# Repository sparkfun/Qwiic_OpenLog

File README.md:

SparkFun Qwiic OpenLog
========================================

[*SparkFun Qwiic OpenLog (DEV-15164)*](https://www.sparkfun.com/products/15164)

The [Qwiic](https://www.sparkfun.com/qwiic) system makes it easy to read all sorts of sensors, but what if you want to log that data? Qwiic OpenLog is an easy to use I2C based data logger. Simply write code like:

    recordToOpenLog("The battery voltage is:");
    recordToOpenLog(batteryVoltage);

And your data will be recorded to LOG00001.TXT for later review. 

The SparkFun Qwiic OpenLog is the smarter and better looking cousin to the extremely popular [OpenLog](https://www.sparkfun.com/products/13712). We've ported the serial based interface to I2C. Now you can daisy chain lots of I2C devices and log them all without taking up your serial port.

We've written a large number of example sketches to show how to record logs, create new logs, create and navigate directories, remove files and directories, and read the contents of files. 

Qwiic OpenLog supports clock stretching which means it performs even better than the original! Qwiic OpenLog will record data up to 21,000 bytes per second at 400kHz. As the receive buffer fills up QOL will hold the clock line letting the master know that it is busy. Once QOL is finished with a task it releases the clock allowing the data to continue flowing without corruption.

Need to get freaky and have multiple data loggers on the same bus? You're in luck. Qwiic OpenLog has both a solder jumper to allow for two devices on the same bus as well as a software setting to allow for the setting of any I2C address. Don't get too freaky though; the limit is 111 devices (0x08 to 0x77) on the same bus. Any microSD card will work so with 64GB cards you'll be limited to approximately 7 Terabytes of storage :(

We will be adding more features to the firmware over time and we've made it very easy to upgrade! If you're comfortable sending a sketch to an Uno then you can upgrade the firmware on Qwiic OpenLog.

Repository Contents
-------------------

* **/Firmware/Qwiic_OpenLog** - The core sketch that runs Qwiic OpenLog
* **/Hardware** - Eagle design files (.brd, .sch)

Documentation
--------------
* **[Library](https://github.com/sparkfun/SparkFun_Qwiic_OpenLog_Arduino_Library)** - Arduino library for the Qwiic OpenLog.
* **[Hookup Guide](https://learn.sparkfun.com/tutorials/qwiic-openlog-hookup-guide)** - Basic hookup guide for the Qwiic OpenLog.
* **[SparkFun Fritzing repo](https://github.com/sparkfun/Fritzing_Parts)** - Fritzing diagrams for SparkFun products.

License Information
-------------------

This product is _**open source**_! 

Please review the LICENSE.md file for license information. 

If you have any questions or concerns on licensing, please contact techsupport@sparkfun.com.

Please use, reuse, and modify these files as you see fit. Please maintain attribution to SparkFun Electronics and release any derivative under the same license.

Distributed as-is; no warranty is given.

- Your friends at SparkFun.

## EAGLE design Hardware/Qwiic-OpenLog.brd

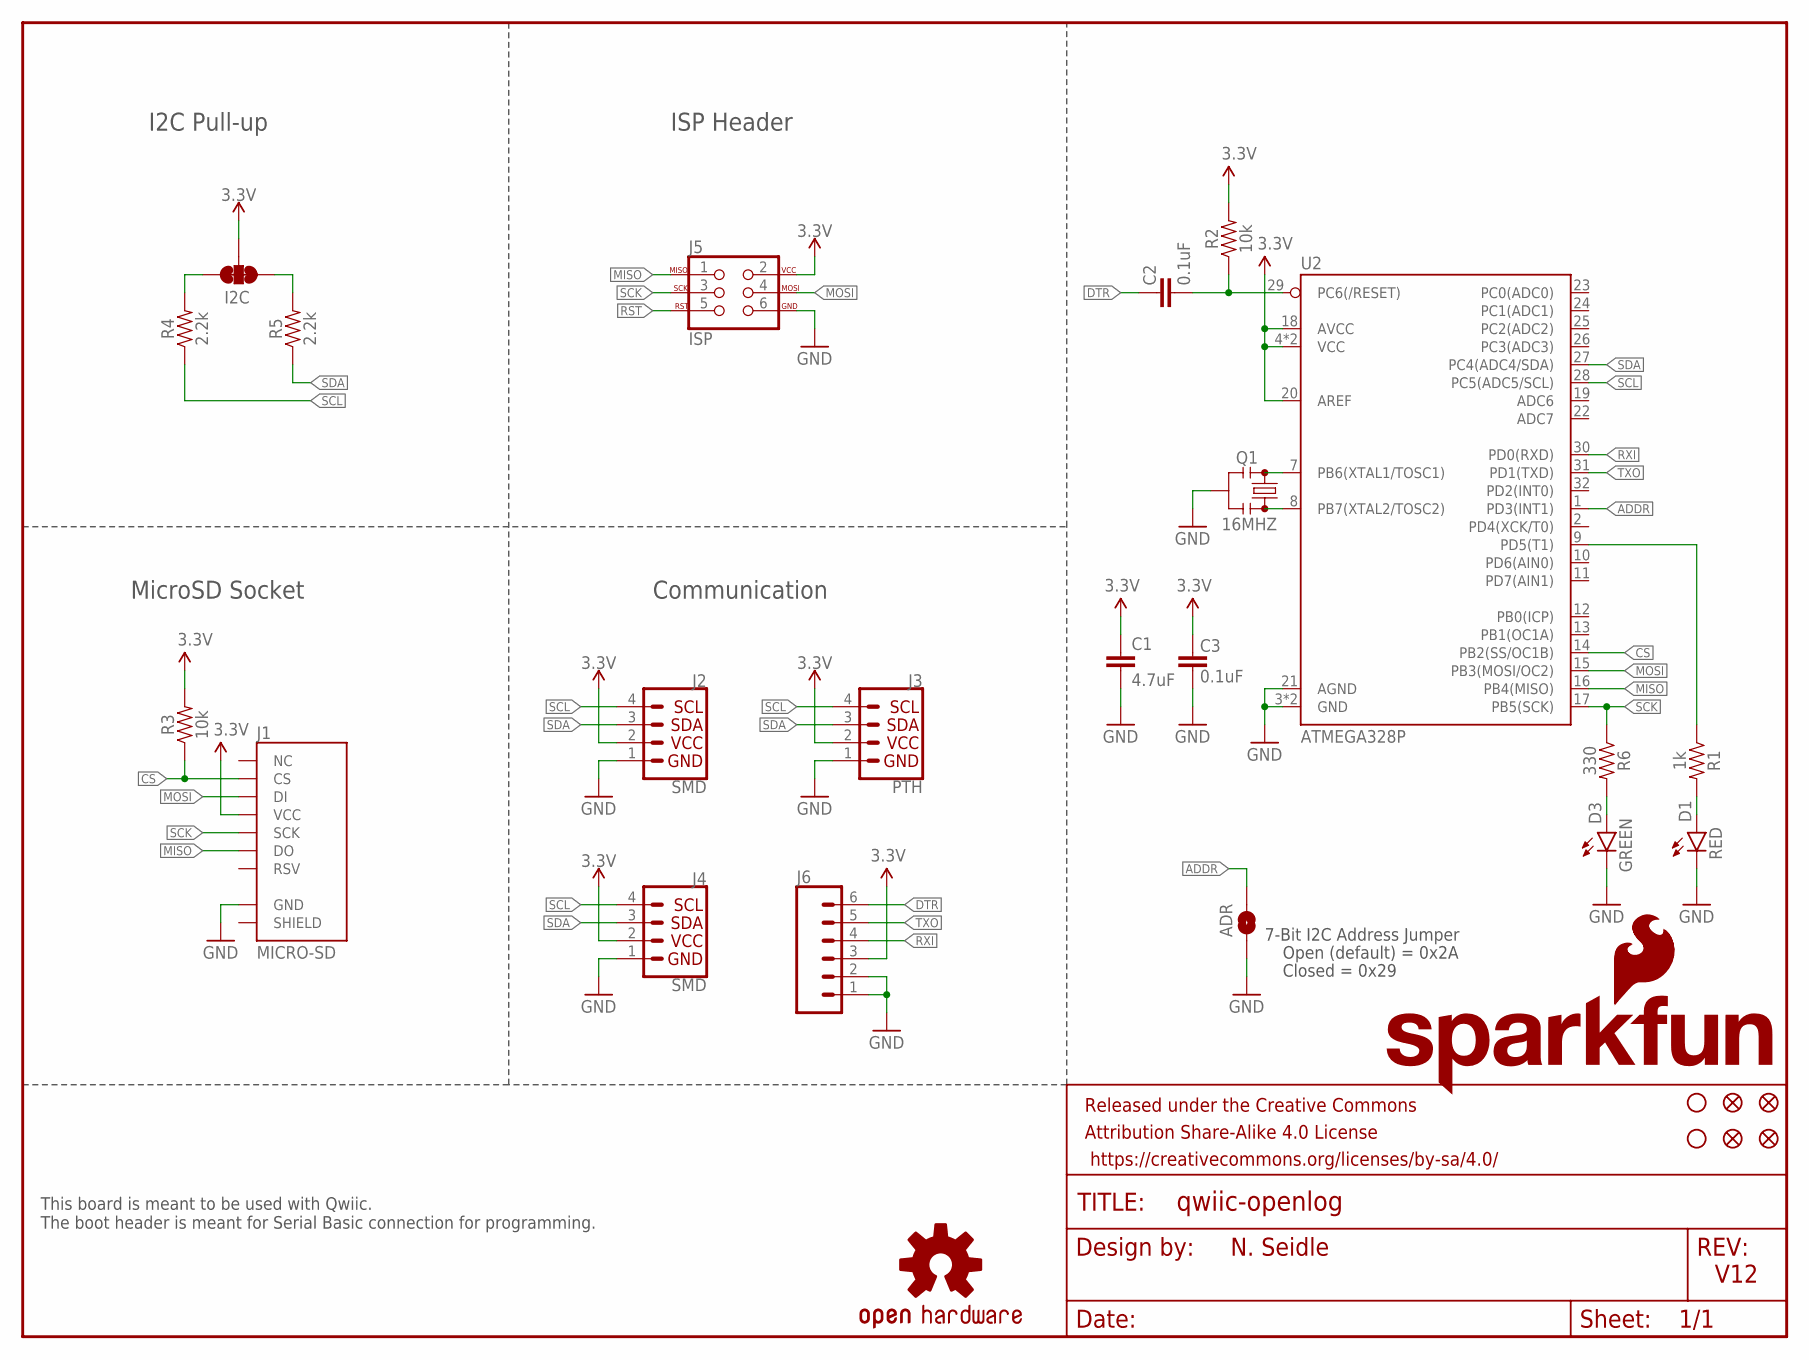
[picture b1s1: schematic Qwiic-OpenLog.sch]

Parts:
ADR: SOLDERJUMPERNO; SJ_2S-NO
C1: 4.7uF; 0603
C2, C3: 0.1uF; 0603
D1: RED; LED-0603
D3: GREEN; LED-0603
FID1, FID2, FID3, FID4: FIDUCIALUFIDUCIAL; FIDUCIAL-MICRO
FRAME1: FRAME-LETTER; CREATIVE_COMMONS
I2C: JUMPER-SMT_3_2-NC_TRACE_SILK; SMT-JUMPER_3_2-NC_TRACE_SILK
J1: MICRO-SD; MICRO-SD-SOCKET
J2, J4: SMD; 1X04_1MM_RA
J3: PTH; 1X04_NO_SILK
J5: ISP; 2X3_TEST_POINTS
J6: CONN_06NO_SILK_NO_POP; 1X06_NO_SILK
JP3, JP4: STAND-OFF
LOGO1: SFE_LOGO_FLAME.1_INCH; SFE_LOGO_FLAME_.1
LOGO2: OSHW-LOGOMINI; OSHW-LOGO-MINI
LOGO4: SFE_LOGO_NAME_FLAME.1_INCH; SFE_LOGO_NAME_FLAME_.1
Q1: 16MHZ; RESONATOR-SMD
R1: 1k; 0603
R2, R3: 10k; 0603
R4, R5: 2.2k; 0603
R6: 330; 0603
U2: ATMEGA328P; TQFP32-08

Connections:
3.3V: C1.1, C3.2, I2C.2, J1.VCC, J2.2, J3.2 (VCC), J4.2, J5.2, J6.3, R2.2, R3.2, U2.4 (VCC), U2.6 (VCC), U2.18 (AVCC), U2.20 (AREF)
ADDR: ADR.2, U2.1 (PD3(INT1))
CS: J1.CS, R3.1, U2.14 (PB2(SS/OC1B))
DTR: C2.2, J6.6
GND: ADR.1, C1.2, C3.1, D1.C, D3.C, J1.GND, J2.1, J3.1 (GND), J4.1, J5.6, J6.1, J6.2, Q1.2, U2.3 (GND), U2.5 (GND), U2.21 (AGND)
MISO: J1.DO, J5.1, U2.16 (PB4(MISO))
MOSI: J1.DI, J5.4, U2.15 (PB3(MOSI/OC2))
unnamed: Q1.1, U2.8 (PB7(XTAL2/TOSC2))
unnamed: Q1.3, U2.7 (PB6(XTAL1/TOSC1))
unnamed: D1.A, R1.2
unnamed: R1.1, U2.9 (PD5(T1))
unnamed: I2C.1, R5.2
unnamed: I2C.3, R4.2
unnamed: D3.A, R6.2
RST: C2.1, J5.5, R2.1, U2.29 (PC6(/RESET))
RXI: J6.4, U2.30 (PD0(RXD))
SCK: J1.SCLK (SCK), J5.3, R6.1, U2.17 (PB5(SCK))
SCL: J2.4, J3.4 (SCL), J4.4, R4.1, U2.28 (PC5(ADC5/SCL))
SDA: J2.3, J3.3 (SDA), J4.3, R5.1, U2.27 (PC4(ADC4/SDA))
TXO: J6.5, U2.31 (PD1(TXD))

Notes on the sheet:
This board is meant to be used with Qwiic. The boot header is meant for Serial Basic connection for programming.
V12
N. Seidle
I2C Pull-up
Communication
MicroSD Socket
ISP Header
7-Bit I2C Address Jumper
Closed = 0x29
Open (default) = 0x2A

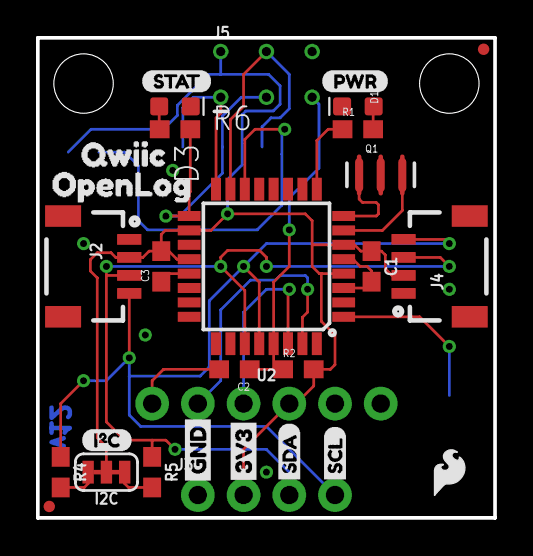
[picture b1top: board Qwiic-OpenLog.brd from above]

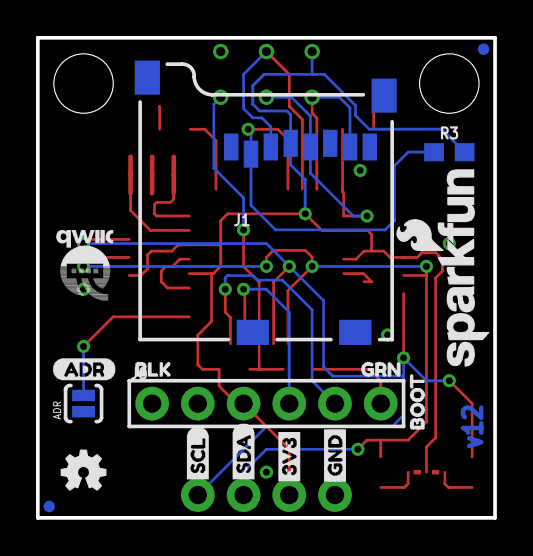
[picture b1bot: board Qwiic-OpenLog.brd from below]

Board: 2 copper layers, 25.4 x 26.7 mm, 49 parts (17 on the bottom side), 20 nets.

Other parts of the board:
U$3: QWIIC-LOGO-SMALL
U$4: 3V3-03
U$5: GND-03
U$6: 3V30
U$7: ADR-()-03
U$8: I_SUPER2_C-()-03
U$9: PWR-()-03
U$10: BLK3
U$11: BOOT5
U$12: GRN4
U$13, U$16: SDA1
U$14: QWIIC7
U$15, U$19: SCL2
U$17: STAT0
U$18: OPENLOG0
U$20: GND1

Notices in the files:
parts and their libraries:
SparkFun-Connectors: Licensing: Creative Commons ShareAlike 4.0 International - https://creativecommons.org/licenses/by-sa/4.0
SparkFun-Aesthetics: Released under the Creative Commons Attribution Share-Alike 4.0 License
SparkFun-Aesthetics: https://creativecommons.org/licenses/by-sa/4.0
